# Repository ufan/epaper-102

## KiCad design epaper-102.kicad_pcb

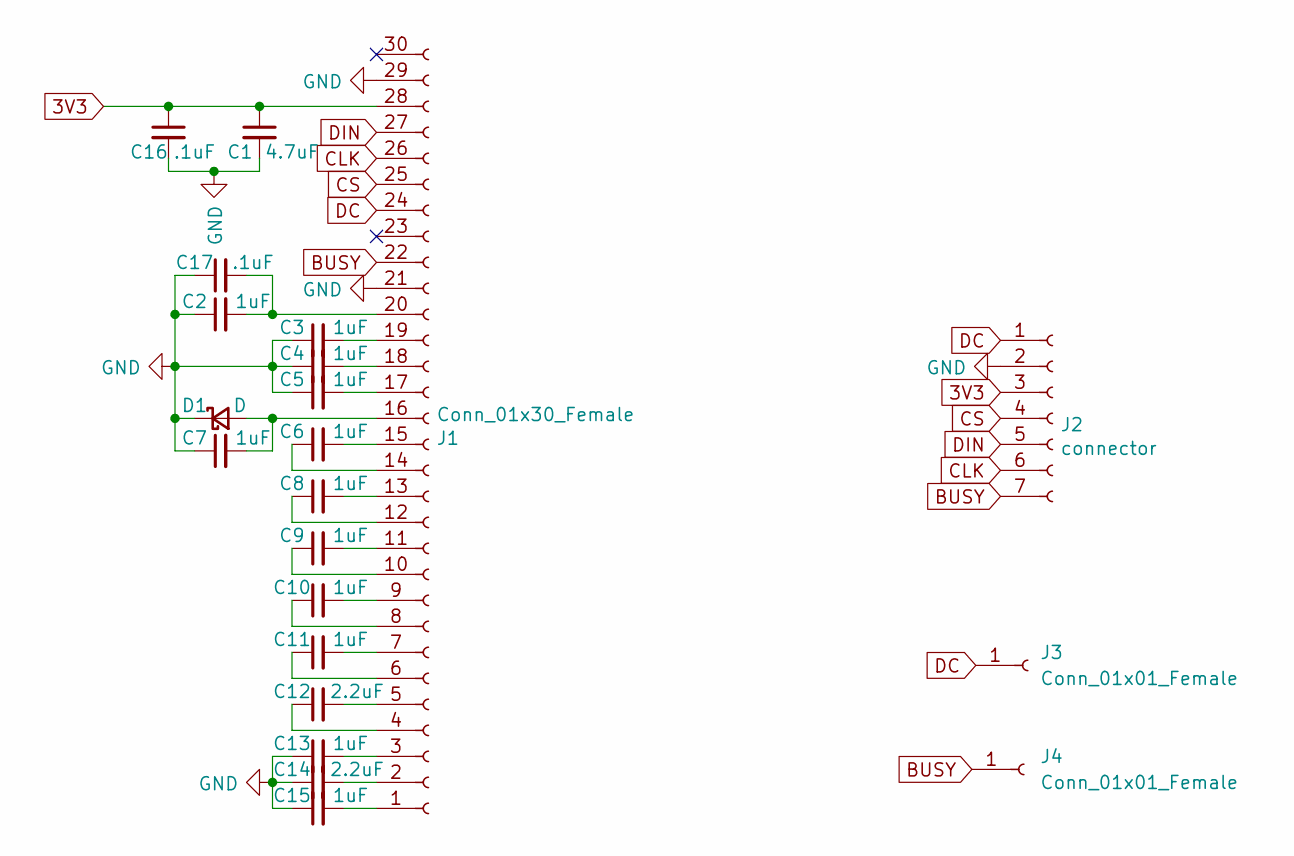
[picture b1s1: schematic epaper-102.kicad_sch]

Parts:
C1: 4.7uF; C_0402_1005Metric; LCSC C23733
C2, C3, C4, C5, C6, C7, C8, C9, C10, C11, C13, C15: 1uF; C_0402_1005Metric; LCSC C52923
C12, C14: 2.2uF; C_0603_1608Metric; LCSC C23630
C16, C17: .1uF; C_0402_1005Metric; LCSC C1525
D1: D; D_SOD-123; LCSC C8598
J1: Conn_01x30_Female; Hirose_FH12-30S-0.5SH_1x30-1MP_P0.50mm_Horizontal; LCSC C262294
J2: connector; PinHeader_1x07_P2.54mm_Vertical
J3, J4: Conn_01x01_Female; PinHeader_1x01_P2.54mm_Vertical

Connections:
3V3: C1.1, C16.1, J1.28, J2.3
BUSY: J1.22, J2.7, J4.1
CLK: J1.26, J2.6
CS: J1.25, J2.4
DC: J1.24, J2.1, J3.1
DIN: J1.27, J2.5
GND: C1.2, C2.1, C3.1, C4.1, C5.1, C7.1, C13.1, C14.1, C15.1, C16.2, C17.1, D1.1 (K), J1.21, J1.29, J2.2
unnamed: C3.2, J1.19
unnamed: C4.2, J1.18
unnamed: C5.2, J1.17
unnamed: C6.1, J1.14
unnamed: C6.2, J1.15
unnamed: C7.2, D1.2 (A), J1.16
unnamed: C8.1, J1.12
unnamed: C8.2, J1.13
unnamed: C9.1, J1.10
unnamed: C9.2, J1.11
unnamed: C10.1, J1.8
unnamed: C10.2, J1.9
unnamed: C11.1, J1.6
unnamed: C11.2, J1.7
unnamed: C12.1, J1.4
unnamed: C12.2, J1.5
unnamed: C13.2, J1.3
unnamed: C14.2, J1.2
unnamed: C15.2, J1.1
unnamed: C2.2, C17.2, J1.20

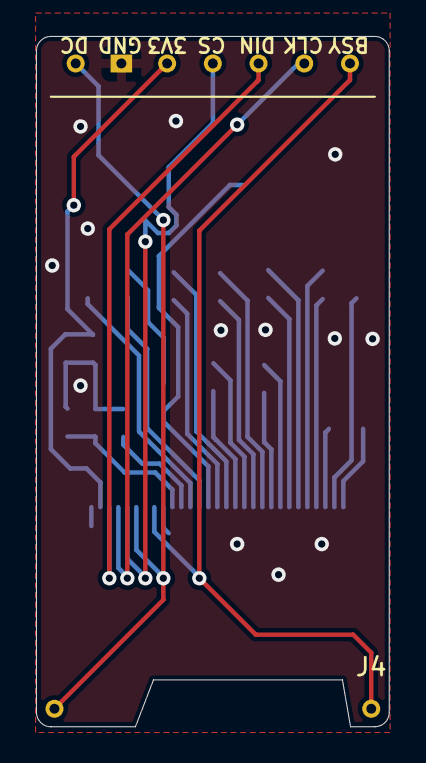
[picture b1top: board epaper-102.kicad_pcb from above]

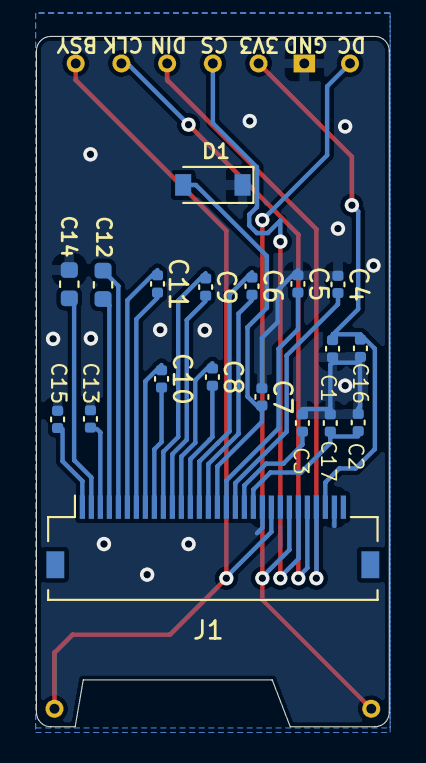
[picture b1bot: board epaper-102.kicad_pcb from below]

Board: 2 copper layers, 19.6 x 38.4 mm, 22 parts (19 on the bottom side), 27 nets.

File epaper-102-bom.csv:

"Item","Qty","Reference(s)","Value","LibPart","Footprint","Datasheet","LCSC"
"1","1","C1","4.7uF","Device:C_Small","Capacitor_SMD:C_0402_1005Metric","~","C23733"
"2","12","C2, C3, C4, C5, C6, C7, C8, C9, C10, C11, C13, C15","1uF","Device:C_Small","Capacitor_SMD:C_0402_1005Metric","~","C52923"
"3","2","C12, C14","2.2uF","Device:C_Small","Capacitor_SMD:C_0603_1608Metric","~","C23630"
"4","1","D1","D","Device:D_Schottky_Small","Diode_SMD:D_SOD-123","~","C8598", "B5819W"
"5","1","J1","Conn_01x30_Female","Connector:Conn_01x30_Female","Connector_FFC-FPC:Hirose_FH12-30S-0.5SH_1x30-1MP_P0.50mm_Horizontal","~","C262294"
"6","1","J2","Conn_01x08_Female","Connector:Conn_01x08_Female","PinHeader_1x08_P2.54mm_Vertical","~","height: 2mm"
"7","2","C16, C17","100nF","Device:C_Small","Capacitor_SMD:C_0402_1005Metric","~","C1525"

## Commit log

2022-05-07 bugfix: J2 should be P2.54
2022-07-01 change package to 0603
2022-09-10 backup
2022-09-10 add ibom
2022-09-13 add two mounting socket and optimize the the dimensions
2022-09-13 add v4.0 gerber
